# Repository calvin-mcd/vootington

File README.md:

# Vootington

The Vootington is an open source hall-effect pcb for the V4N keyboard.

The aim of this project is to offer a functional hardware Hall-effect reference project for the community. The project is not meant to offer the full aspects of firmware. I leave that to smart people to figure out.

The keyboard takes design cues from the Wooting keyboards, [the moonpad](https://github.com/RephlexZero/MoonPad) and [the void switch keyboards](https://github.com/riskable/void_switch_65_pct) from riskable.

## Layout

[Link](http://www.keyboard-layout-editor.com/#/gists/a01bb022278fa95758b773367ecef891)

## Firmware

The basic firmware included in the folder is experimental and designed by KarlK90. Their work can be found here:
https://github.com/KarlK90/qmk_firmware/tree/feature/vootington/keyboards/calvin0563/vootington

Pete is currently developing more advanced HE firmware for zmk. Keep your eyes on that:
https://github.com/petejohanson/vootington-zmk-config

**beware!!!**

The hardware configuration for rgb on the vootington is currently not supported by zmk, which means no rgb with the zmk firmware.

## Todo

- [ ] create advanced firmware with full HE functionality

## Disclaimer

This PCB has been fully tested and is confirmed to work. However, no-one involved in this project is responsible for any usage issues that may arise. Order at your own risk. Feel free to edit, modify and otherwise utilise these files.

## License

This project is released under the GPL v3 License. Please refer to the LICENCE file.

## Credits

big thanks to KarlK90 for making the initial firmware and for supporting the hardware design of the keyboard.

another huge thanks to pete for writing zmk firmware for this!

As always big thanks also to the many people who helped to inspire this board!

Any questions, contact Calvin0563 on Discord.

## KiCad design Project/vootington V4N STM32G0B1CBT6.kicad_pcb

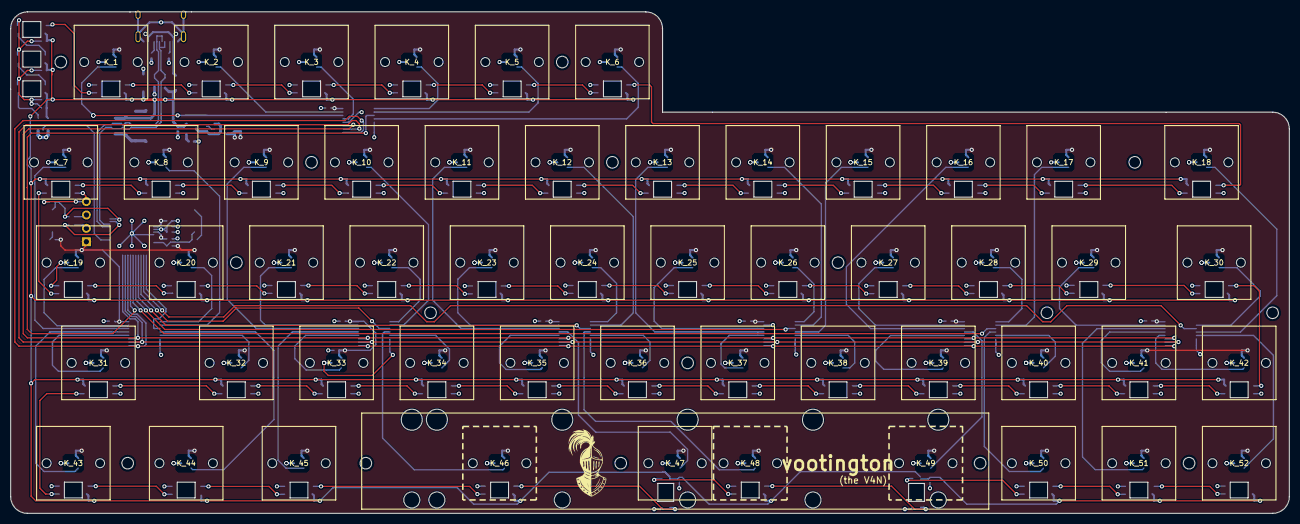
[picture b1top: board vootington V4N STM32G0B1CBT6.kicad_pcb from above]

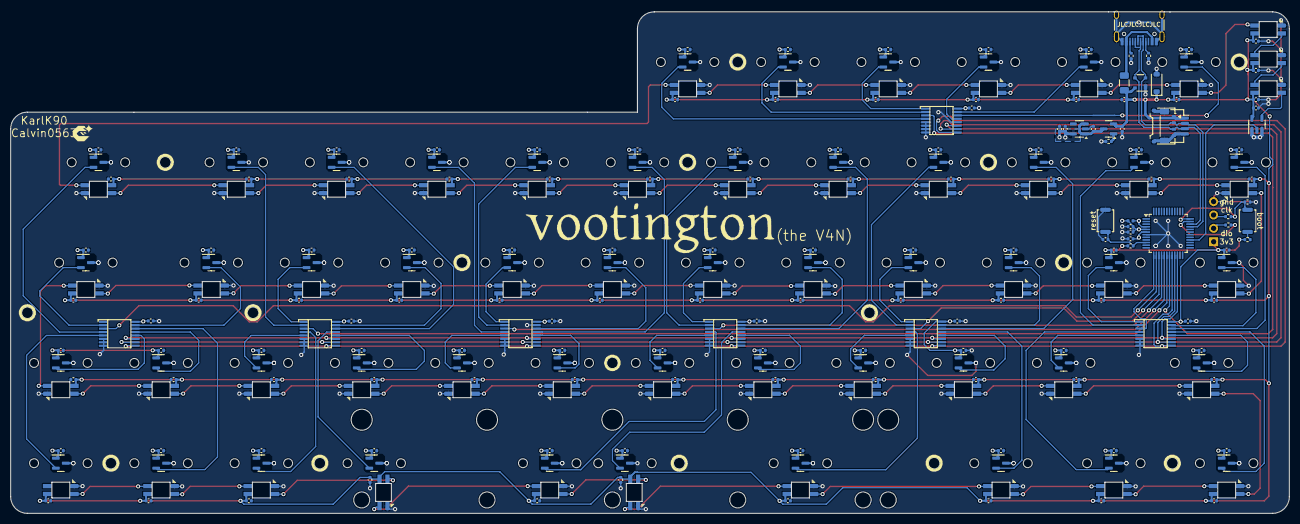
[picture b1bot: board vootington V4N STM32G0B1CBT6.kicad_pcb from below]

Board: 2 copper layers, 242.9 x 95.2 mm, 331 parts (260 on the bottom side), 135 nets.

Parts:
C1, C2, C3, C4, C5, C6, C7, C8, C9, C10, C11, C12, C13, C14, C15, C16, C17, C18, C19, C20, C21, C22, C23, C24, C25, C26, C27, C28, C29, C30, C31, C32, C33, C34, C35, C36, C37, C38, C39, C40, C41, C42, C43, C44, C45, C46, C47, C48, C49, C50, C51, C52, C53, C56, C60, C61, C62, C63, C64, C65, C66, C67, C68, C69, C70, C71, C72, C73, C74, C75, C76, C77, C78, C79, C80, C81, C82, C83, C84, C85, C86, C87, C88, C89, C90, C91, C92, C93, C94, C95, C96, C97, C98, C99, C100, C101, C102, C103, C104, C105, C106, C107, C108, C109, C110, C111, C112, C113, C114, C115, C116, C117: 100nF; C_0402_1005Metric
C54: 10nF; C_0402_1005Metric
C55: 1uF; C_0402_1005Metric
C57, C58: 10uF; C_0402_1005Metric
C59: 2.2uF; C_0402_1005Metric
C118, C119, C120, C121, C122, C123, C124: 100pF; C_0402_1005Metric
D1, D2, D3, D4, D5, D6, D7, D8, D9, D10, D11, D12, D13, D14, D15, D16, D17, D18, D19, D20, D21, D22, D23, D24, D25, D26, D27, D28, D29, D30, D31, D32, D33, D34, D35, D36, D37, D38, D39, D40, D41, D42, D43, D44, D45, D46, D47, D48, D49, D50, D51, D52, D53, D54, D55: YS-SK6803MINI-E; SK6803-MINI-E
D_PWR1: SMF9.0CA; D_SOD-123
F1: 500mA; Fuse_1206_3216Metric
FB1: 1k OHM 100mhz; Fuse_0402_1005Metric
H1, H2, H3, H4, H5, H6, H7, H8, H9, H10, H11, H12, H13, H14, H15, H16: MountingHole; HOLE_M2
J1: Conn_01x04; PinHeader_1x04_P2.54mm_Vertical
J2: USB_C sink board 1.3mm; USB_C_Receptacle_HRO_TYPE-C-31-M-12
J3: JST SH; JST_SH_SM04B-SRSS-TB_1x04-1MP_P1.00mm_Horizontal
J4: Pico EZmate; Molex_Pico-EZmate_78171-0004_1x04-1MP_P1.20mm_Vertical
K_1, K_2, K_3, K_4, K_5, K_6, K_7, K_8, K_9, K_10, K_11, K_12, K_13, K_14, K_15, K_16, K_17, K_18, K_19, K_20, K_21, K_22, K_23, K_24, K_25, K_26, K_27, K_28, K_29, K_30, K_31, K_32, K_33, K_34, K_35, K_36, K_37, K_38, K_39, K_40, K_41, K_42, K_43, K_44, K_45, K_46, K_47, K_48, K_49, K_50, K_51, K_52: KEYSW; Wooting_1.00u
Q1: AP40P05; SOT-23
R1, R2: 33 Ohm; R_0402_1005Metric
R3, R5, R6: 10k; R_0402_1005Metric
R4: 330 Ohm; R_0402_1005Metric
R7, R8: 5.1k; R_0402_1005Metric
S1: MX_stab; STAB_MX_2.75u
S2: MX_stab; STAB_MX_6.25u
S3: MX_stab; STAB_MX_2.25u
SW1, SW2: Alps SKRK; SW_Push_SPST_NO_Alps_SKRK
U1, U2, U3, U4, U5, U6, U7, U8, U9, U10, U11, U12, U13, U14, U15, U16, U17, U18, U19, U20, U21, U22, U23, U24, U25, U26, U27, U28, U29, U30, U31, U32, U33, U34, U35, U36, U37, U38, U39, U40, U41, U42, U43, U44, U45, U46, U47, U48, U49, U50, U51, U52: SLSS49E-3; SOT-23
U53: STM32G0B1CBTx; LQFP-48_7x7mm_P0.5mm
U54: AP2112K-3.3; SOT-23-5
U55: PRTR5V0U2X; SOT-143
U56: 74AHCT1G125; TSOT-23-5
U57, U58, U59, U60, U61, U62, U63: 74HC4051; TSSOP16

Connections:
+3V3: C1.1, C2.1, C3.1, C4.1, C5.1, C6.1, C7.1, C8.1, C9.1, C10.1, C11.1, C12.1, C13.1, C14.1, C15.1, C16.1, C17.1, C18.1, C19.1, C20.1, C21.1, C22.1, C23.1, C24.1, C25.1, C26.1, C27.1, C28.1, C29.1, C30.1, C31.1, C32.1, C33.1, C34.1, C35.1, C36.1, C37.1, C38.1, C39.1, C40.1, C41.1, C42.1, C43.1, C44.1, C45.1, C46.1, C47.1, C48.1, C49.1, C50.1, C51.1, C52.1, C53.1, C58.2, C59.2, C118.1, C119.1, C120.1, C121.1, C122.1, C123.1, C124.1, FB1.1, J1.1, R3.1, R4.1, U1.1 (VDD), U2.1 (VDD), U3.1 (VDD), U4.1 (VDD), U5.1 (VDD), U6.1 (VDD), U7.1 (VDD), U8.1 (VDD), U9.1 (VDD), U10.1 (VDD), U11.1 (VDD), U12.1 (VDD), U13.1 (VDD), U14.1 (VDD), U15.1 (VDD), U16.1 (VDD), U17.1 (VDD), U18.1 (VDD), U19.1 (VDD), U20.1 (VDD), U21.1 (VDD), U22.1 (VDD), U23.1 (VDD), U24.1 (VDD), U25.1 (VDD), U26.1 (VDD), U27.1 (VDD), U28.1 (VDD), U29.1 (VDD), U30.1 (VDD), U31.1 (VDD), U32.1 (VDD), U33.1 (VDD), U34.1 (VDD), U35.1 (VDD), U36.1 (VDD), U37.1 (VDD), U38.1 (VDD), U39.1 (VDD), U40.1 (VDD), U41.1 (VDD), U42.1 (VDD), U43.1 (VDD), U44.1 (VDD), U45.1 (VDD), U46.1 (VDD), U47.1 (VDD), U48.1 (VDD), U49.1 (VDD), U50.1 (VDD), U51.1 (VDD), U52.1 (VDD), U53.4 (VBAT), U53.6 (VDD), U54.5 (VOUT), U57.16 (VCC), U58.16 (VCC), U59.16 (VCC), U60.16 (VCC), U61.16 (VCC), U62.16 (VCC), U63.16 (VCC)
+5V: C60.2, C61.1, C62.1, C63.1, C64.1, C65.2, C66.1, C67.1, C68.1, C69.1, C70.1, C71.1, C72.1, C73.1, C74.1, C75.1, C76.1, C77.1, C78.1, C79.1, C80.1, C81.1, C82.1, C83.1, C84.1, C85.1, C86.1, C87.1, C88.1, C89.1, C90.1, C91.1, C92.1, C93.1, C94.1, C95.1, C96.1, C97.1, C98.1, C99.1, C100.1, C101.1, C102.1, C103.1, C104.1, C105.1, C106.1, C107.1, C108.1, C109.1, C110.1, C111.1, C112.1, C113.1, C114.1, C115.1, C116.1, C117.1, D1.3 (VDD), D2.3 (VDD), D3.3 (VDD), D4.3 (VDD), D5.3 (VDD), D6.3 (VDD), D7.3 (VDD), D8.3 (VDD), D9.3 (VDD), D10.3 (VDD), D11.3 (VDD), D12.3 (VDD), D13.3 (VDD), D14.3 (VDD), D15.3 (VDD), D16.3 (VDD), D17.3 (VDD), D18.3 (VDD), D19.3 (VDD), D20.3 (VDD), D21.3 (VDD), D22.3 (VDD), D23.3 (VDD), D24.3 (VDD), D25.3 (VDD), D26.3 (VDD), D27.3 (VDD), D28.3 (VDD), D29.3 (VDD), D30.3 (VDD), D31.3 (VDD), D32.3 (VDD), D33.3 (VDD), D34.3 (VDD), D35.3 (VDD), D36.3 (VDD), D37.3 (VDD), D38.3 (VDD), D39.3 (VDD), D40.3 (VDD), D41.3 (VDD), D42.3 (VDD), D43.3 (VDD), D44.3 (VDD), D45.3 (VDD), D46.3 (VDD), D47.3 (VDD), D48.3 (VDD), D49.3 (VDD), D50.3 (VDD), D51.3 (VDD), D52.3 (VDD), D53.3 (VDD), D54.3 (VDD), D55.3 (VDD), D_PWR1.1 (A1), F1.2, J3.1, J4.1, Q1.2 (S), U55.4 (VCC), U56.5 (VCC)
/MCU/VREF: C54.1, C55.1, FB1.2, U53.5 (VREF+)
ADC0: U53.14 (PA3), U57.3 (A)
ADC1: U53.18 (PA7), U58.3 (A)
ADC2: U53.17 (PA6), U59.3 (A)
ADC3: U53.16 (PA5), U60.3 (A)
ADC4: U53.15 (PA4), U61.3 (A)
ADC5: U53.13 (PA2), U62.3 (A)
ADC6: U53.19 (PB0), U63.3 (A)
BOOT0: R2.1, R5.1, SW1.2, U53.36 (PA14)
D_N: J2.A7 (D-), J2.B7 (D-), J3.2, J4.2, U53.33 (PA11/PA9), U55.2 (I/O1)
D_P: J2.A6 (D+), J2.B6 (D+), J3.3, J4.3, U53.34 (PA12/PA10), U55.3 (I/O2)
GND: C1.2, C2.2, C3.2, C4.2, C5.2, C6.2, C7.2, C8.2, C9.2, C10.2, C11.2, C12.2, C13.2, C14.2, C15.2, C16.2, C17.2, C18.2, C19.2, C20.2, C21.2, C22.2, C23.2, C24.2, C25.2, C26.2, C27.2, C28.2, C29.2, C30.2, C31.2, C32.2, C33.2, C34.2, C35.2, C36.2, C37.2, C38.2, C39.2, C40.2, C41.2, C42.2, C43.2, C44.2, C45.2, C46.2, C47.2, C48.2, C49.2, C50.2, C51.2, C52.2, C53.2, C54.2, C55.2, C56.2, C57.1, C58.1, C59.1, C60.1, C61.2, C62.2, C63.2, C64.2, C65.1, C66.2, C67.2, C68.2, C69.2, C70.2, C71.2, C72.2, C73.2, C74.2, C75.2, C76.2, C77.2, C78.2, C79.2, C80.2, C81.2, C82.2, C83.2, C84.2, C85.2, C86.2, C87.2, C88.2, C89.2, C90.2, C91.2, C92.2, C93.2, C94.2, C95.2, C96.2, C97.2, C98.2, C99.2, C100.2, C101.2, C102.2, C103.2, C104.2, C105.2, C106.2, C107.2, C108.2, C109.2, C110.2, C111.2, C112.2, C113.2, C114.2, C115.2, C116.2, C117.2, C118.2, C119.2, C120.2, C121.2, C122.2, C123.2, C124.2, D1.1 (VSS), D2.1 (VSS), D3.1 (VSS), D4.1 (VSS), D5.1 (VSS), D6.1 (VSS), D7.1 (VSS), D8.1 (VSS), D9.1 (VSS), D10.1 (VSS), D11.1 (VSS), D12.1 (VSS), D13.1 (VSS), D14.1 (VSS), D15.1 (VSS), D16.1 (VSS), D17.1 (VSS), D18.1 (VSS), D19.1 (VSS), D20.1 (VSS), D21.1 (VSS), D22.1 (VSS), D23.1 (VSS), D24.1 (VSS), D25.1 (VSS), D26.1 (VSS), D27.1 (VSS), D28.1 (VSS), D29.1 (VSS), D30.1 (VSS), D31.1 (VSS), D32.1 (VSS), D33.1 (VSS), D34.1 (VSS), D35.1 (VSS), D36.1 (VSS), D37.1 (VSS), D38.1 (VSS), D39.1 (VSS), D40.1 (VSS), D41.1 (VSS), D42.1 (VSS), D43.1 (VSS), D44.1 (VSS), D45.1 (VSS), D46.1 (VSS), D47.1 (VSS), D48.1 (VSS), D49.1 (VSS), D50.1 (VSS), D51.1 (VSS), D52.1 (VSS), D53.1 (VSS), D54.1 (VSS), D55.1 (VSS), D_PWR1.2 (A2), J1.4, J2.A1 (GND), J2.A12 (GND), J2.B1 (GND), J2.B12 (GND), J2.S1 (SHIELD), J3.4, J3.MP (MountPin), J4.4, J4.MP (MountPin), R5.2, R6.1, R7.1, R8.1, SW2.2, U1.3 (GND), U2.3 (GND), U3.3 (GND), U4.3 (GND), U5.3 (GND), U6.3 (GND), U7.3 (GND), U8.3 (GND), U9.3 (GND), U10.3 (GND), U11.3 (GND), U12.3 (GND), U13.3 (GND), U14.3 (GND), U15.3 (GND), U16.3 (GND), U17.3 (GND), U18.3 (GND), U19.3 (GND), U20.3 (GND), U21.3 (GND), U22.3 (GND), U23.3 (GND), U24.3 (GND), U25.3 (GND), U26.3 (GND), U27.3 (GND), U28.3 (GND), U29.3 (GND), U30.3 (GND), U31.3 (GND), U32.3 (GND), U33.3 (GND), U34.3 (GND), U35.3 (GND), U36.3 (GND), U37.3 (GND), U38.3 (GND), U39.3 (GND), U40.3 (GND), U41.3 (GND), U42.3 (GND), U43.3 (GND), U44.3 (GND), U45.3 (GND), U46.3 (GND), U47.3 (GND), U48.3 (GND), U49.3 (GND), U50.3 (GND), U51.3 (GND), U52.3 (GND), U53.7 (VSS), U54.2 (GND), U55.1 (GND), U56.1, U56.3 (GND), U57.6 (~E), U57.7 (VEE), U57.8 (GND), U58.6 (~E), U58.7 (VEE), U58.8 (GND), U59.6 (~E), U59.7 (VEE), U59.8 (GND), U59.15 (A2), U60.6 (~E), U60.7 (VEE), U60.8 (GND), U61.6 (~E), U61.7 (VEE), U61.8 (GND), U62.6 (~E), U62.7 (VEE), U62.8 (GND), U63.5 (A5), U63.6 (~E), U63.7 (VEE), U63.8 (GND), U63.12 (A3)
K_1: U7.2 (OUT), U62.14 (A1)
K_2: U8.2 (OUT), U62.2 (A6)
K_3: U9.2 (OUT), U61.14 (A1)
K_4: U10.2 (OUT), U61.2 (A6)
K_5: U11.2 (OUT), U60.14 (A1)
K_6: U12.2 (OUT), U60.2 (A6)
K_7: U13.2 (OUT), U59.13 (A0)
K_8: U14.2 (OUT), U59.2 (A6)
K_9: U15.2 (OUT), U59.4 (A7)
K_10: U16.2 (OUT), U58.14 (A1)
K_11: U18.2 (OUT), U58.2 (A6)
K_12: U17.2 (OUT), U57.4 (A7)
K_13: U19.2 (OUT), U62.15 (A2)
K_14: U20.2 (OUT), U62.1 (A4)
K_15: U21.2 (OUT), U61.15 (A2)
K_16: U22.2 (OUT), U61.1 (A4)
K_17: U23.2 (OUT), U60.15 (A2)
K_18: U24.2 (OUT), U60.1 (A4)
K_19: U25.2 (OUT), U59.14 (A1)
K_20: U26.2 (OUT), U59.1 (A4)
K_21: U27.2 (OUT), U58.15 (A2)
K_22: U28.2 (OUT), U58.1 (A4)
K_23: U29.2 (OUT), U57.15 (A2)
K_24: U30.2 (OUT), U57.2 (A6)
K_25: U31.2 (OUT), U62.12 (A3)
K_26: U32.2 (OUT), U62.5 (A5)
K_27: U33.2 (OUT), U61.12 (A3)
K_28: U34.2 (OUT), U61.5 (A5)
K_29: U35.2 (OUT), U60.12 (A3)
K_30: U36.2 (OUT), U60.5 (A5)
K_31: U37.2 (OUT), U59.12 (A3)
K_32: U38.2 (OUT), U59.5 (A5)
K_33: U39.2 (OUT), U58.12 (A3)
K_34: U40.2 (OUT), U58.5 (A5)
K_35: U41.2 (OUT), U57.13 (A0)
K_36: U42.2 (OUT), U57.12 (A3)
K_37: U43.2 (OUT), U62.13 (A0)
K_38: U44.2 (OUT), U62.4 (A7)
K_39: U45.2 (OUT), U61.13 (A0)
K_40: U46.2 (OUT), U61.4 (A7)
K_41: U47.2 (OUT), U60.13 (A0)
K_42: U48.2 (OUT), U60.4 (A7)
K_43: U49.2 (OUT), U58.13 (A0)
K_44: U50.2 (OUT), U58.4 (A7)
K_45: U51.2 (OUT), U57.14 (A1)
K_46: U52.2 (OUT), U57.5 (A5)
K_48: U1.2 (OUT), U63.14 (A1)
K_49: U2.2 (OUT), U63.15 (A2)
K_50: U3.2 (OUT), U63.13 (A0)
K_51: U4.2 (OUT), U63.1 (A4)
K_52: U5.2 (OUT), U63.2 (A6)
K_53: U6.2 (OUT), U63.4 (A7)
NRST: C56.1, R3.2, SW2.1, U53.10 (PF2)
unnamed: D1.4 (DOUT), D2.2 (DIN)
unnamed: D2.4 (DOUT), D3.2 (DIN)
unnamed: D3.4 (DOUT), D4.2 (DIN)
unnamed: D4.4 (DOUT), D5.2 (DIN)
unnamed: D5.4 (DOUT), D6.2 (DIN)
unnamed: D6.4 (DOUT), D7.2 (DIN)
unnamed: D7.4 (DOUT), D8.2 (DIN)
unnamed: D8.4 (DOUT), D9.2 (DIN)
unnamed: D9.4 (DOUT), D10.2 (DIN)
unnamed: D10.4 (DOUT), D11.2 (DIN)
unnamed: D11.4 (DOUT), D12.2 (DIN)
unnamed: D12.4 (DOUT), D13.2 (DIN)
unnamed: D13.4 (DOUT), D14.2 (DIN)
unnamed: D14.4 (DOUT), D15.2 (DIN)
unnamed: D15.4 (DOUT), D16.2 (DIN)
unnamed: D16.4 (DOUT), D17.2 (DIN)
unnamed: D17.4 (DOUT), D18.2 (DIN)
unnamed: D18.4 (DOUT), D19.2 (DIN)
unnamed: D19.4 (DOUT), D20.2 (DIN)
unnamed: D20.4 (DOUT), D21.2 (DIN)
unnamed: D21.4 (DOUT), D33.2 (DIN)
unnamed: D22.2 (DIN), D23.4 (DOUT)
unnamed: D22.4 (DOUT), D34.2 (DIN)
unnamed: D23.2 (DIN), D24.4 (DOUT)
unnamed: D24.2 (DIN), D25.4 (DOUT)
unnamed: D25.2 (DIN), D26.4 (DOUT)
unnamed: D26.2 (DIN), D27.4 (DOUT)
unnamed: D27.2 (DIN), D28.4 (DOUT)
unnamed: D28.2 (DIN), D29.4 (DOUT)
unnamed: D29.2 (DIN), D30.4 (DOUT)
unnamed: D30.2 (DIN), D31.4 (DOUT)
unnamed: D31.2 (DIN), D32.4 (DOUT)
unnamed: D32.2 (DIN), D33.4 (DOUT)
unnamed: D34.4 (DOUT), D35.2 (DIN)
unnamed: D35.4 (DOUT), D36.2 (DIN)
unnamed: D36.4 (DOUT), D37.2 (DIN)
unnamed: D37.4 (DOUT), D38.2 (DIN)
unnamed: D38.4 (DOUT), D39.2 (DIN)
unnamed: D39.4 (DOUT), D40.2 (DIN)
unnamed: D40.4 (DOUT), D41.2 (DIN)
unnamed: D41.4 (DOUT), D42.2 (DIN)
unnamed: D42.4 (DOUT), D43.2 (DIN)
unnamed: D43.4 (DOUT), D44.2 (DIN)
unnamed: D44.4 (DOUT), D45.2 (DIN)
unnamed: D45.4 (DOUT), D55.2 (DIN)
unnamed: D46.2 (DIN), D47.4 (DOUT)
unnamed: D47.2 (DIN), D48.4 (DOUT)
unnamed: D48.2 (DIN), D49.4 (DOUT)
unnamed: D49.2 (DIN), D50.4 (DOUT)
unnamed: D50.2 (DIN), D51.4 (DOUT)
unnamed: D51.2 (DIN), D52.4 (DOUT)
unnamed: D52.2 (DIN), D53.4 (DOUT)
unnamed: D53.2 (DIN), D54.4 (DOUT)
unnamed: D54.2 (DIN), D55.4 (DOUT)
unnamed: J1.2, R1.2
unnamed: J1.3, R2.2
unnamed: J2.A5 (CC1), R7.2
unnamed: J2.B5 (CC2), R8.2
unnamed: C57.2, Q1.3 (D), U54.1 (VIN), U54.3 (EN)
unnamed: Q1.1 (G), R6.2
unnamed: R4.2, SW1.1
RGB: D1.2 (DIN), U56.4
RGB MCU: U53.28 (PA8), U56.2
SELECT0: U53.22 (PB10), U57.11 (S0), U58.11 (S0), U59.11 (S0), U60.11 (S0), U61.11 (S0), U62.11 (S0), U63.11 (S0)
SELECT1: U53.21 (PB2), U57.10 (S1), U58.10 (S1), U59.10 (S1), U60.10 (S1), U61.10 (S1), U62.10 (S1), U63.10 (S1)
SELECT2: U53.20 (PB1), U57.9 (S2), U58.9 (S2), U59.9 (S2), U60.9 (S2), U61.9 (S2), U62.9 (S2), U63.9 (S2)
SWDIO: R1.1, U53.35 (PA13)
VBUS: F1.1, J2.A4 (VBUS), J2.A9 (VBUS), J2.B4 (VBUS), J2.B9 (VBUS)

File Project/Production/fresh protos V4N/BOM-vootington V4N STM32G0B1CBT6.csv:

Comment,Designator,Footprint,LCSC,Quantity,
330 Ohm,R4,R_0402_1005Metric,C105875,1,
1uF,C55,C_0402_1005Metric,C106254,1,
Alps SKRK,"SW1,SW2",SW_Push_SPST_NO_Alps_SKRK,C115351,2,
1k OHM 100mhz,FB1,Fuse_0402_1005Metric,C76883,1,
33 Ohm,"R1,R2",R_0402_1005Metric,C137880,2,
10nF,C54,C_0402_1005Metric,C1524,1,
JST SH,J3,JST_SH_SM04B-SRSS-TB_1x04-1MP_P1.00mm_Horizontal,C160404,1,
10k,"R3,R5,R6",R_0402_1005Metric,C25744,3,
5.1k,"R7,R8",R_0402_1005Metric,C25905,2,
PRTR5V0U2X,U55,SOT-143,C2827688,1,
STM32G0B1CBTx,U53,LQFP-48_7x7mm_P0.5mm,C2847904,1,
AP40P05,Q1,SOT-23,C2886385,1,
SLSS49E-3,"U1,U10,U11,U12,U13,U14,U15,U16,U17,U18,U19,U2,U20,U21,U22,U23,U24,U25,U26,U27,U28,U29,U3,U30,U31,U32,U33,U34,U35,U36,U37,U38,U39,U4,U40,U41,U42,U43,U44,U45,U46,U47,U48,U49,U5,U50,U51,U52,U6,U7,U8,U9",SOT-23,C2904393,52,
SMF9.0CA,D_PWR1,D_SOD-123,C2980405,1,
USB_C sink board 1.3mm,J2,USB_C_Receptacle_HRO_TYPE-C-31-M-12,C165948,1,
AP2112K-3.3,U54,SOT-23-5,C3021085,1,
100nF,"C1,C10,C100,C101,C102,C103,C104,C105,C106,C107,C108,C109,C11,C110,C111,C112,C113,C114,C115,C116,C117,C118,C119,C12,C120,C121,C122,C123,C124,C13,C14,C15,C16,C17,C18,C19,C2,C20,C21,C22,C23,C24,C25,C26,C27,C28,C29,C3,C30,C31,C32,C33,C34,C35,C36,C37,C38,C39,C4,C40,C41,C42,C43,C44,C45,C46,C47,C48,C49,C5,C50,C51,C52,C53,C56,C6,C61,C62,C63,C64,C65,C66,C67,C68,C69,C7,C70,C71,C72,C73,C74,C75,C76,C77,C78,C79,C8,C80,C81,C82,C83,C84,C85,C86,C87,C88,C89,C9,C90,C91,C92,C93,C94,C95,C96,C97,C98,C99",C_0402_1005Metric,C307331,118,
YS-SK6803MINI-E,"D1,D10,D11,D12,D13,D14,D15,D16,D17,D18,D19,D2,D20,D21,D22,D23,D24,D25,D26,D27,D28,D29,D3,D30,D31,D32,D33,D34,D35,D36,D37,D38,D39,D4,D40,D41,D42,D43,D44,D45,D46,D47,D48,D49,D5,D50,D51,D52,D53,D54,D55,D6,D7,D8,D9",SK6803-MINI-E,C5242955,55,C5242955
10uF,"C57,C58,C59,C60",C_0402_1005Metric,C52923,4,
74HC4051,"U57,U58,U59,U60,U61,U62,U63",TSSOP16,C5645,7,
500mA,F1,Fuse_1206_3216Metric,C369160,1,
74AHCT1G125,U56,TSOT-23-5,C7468,1,

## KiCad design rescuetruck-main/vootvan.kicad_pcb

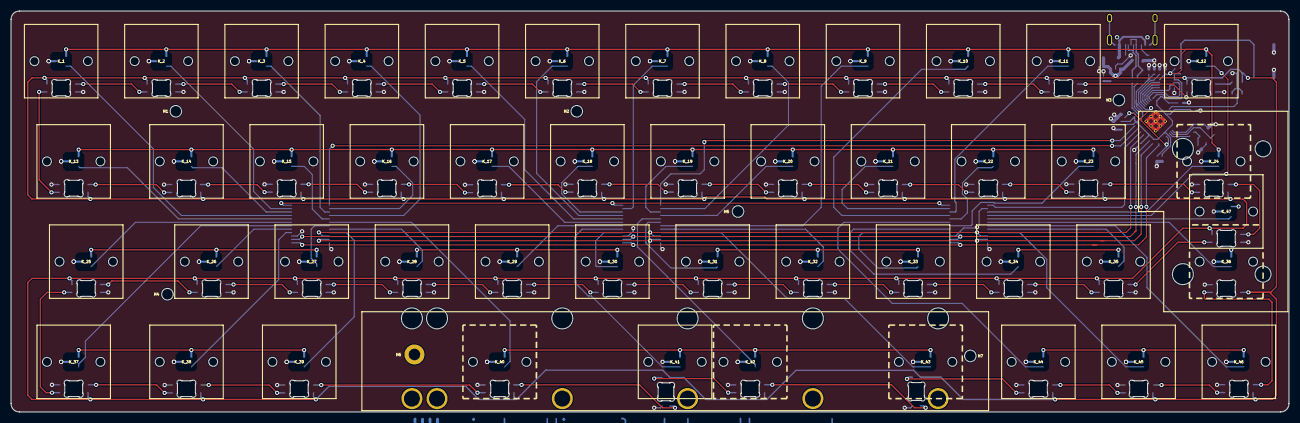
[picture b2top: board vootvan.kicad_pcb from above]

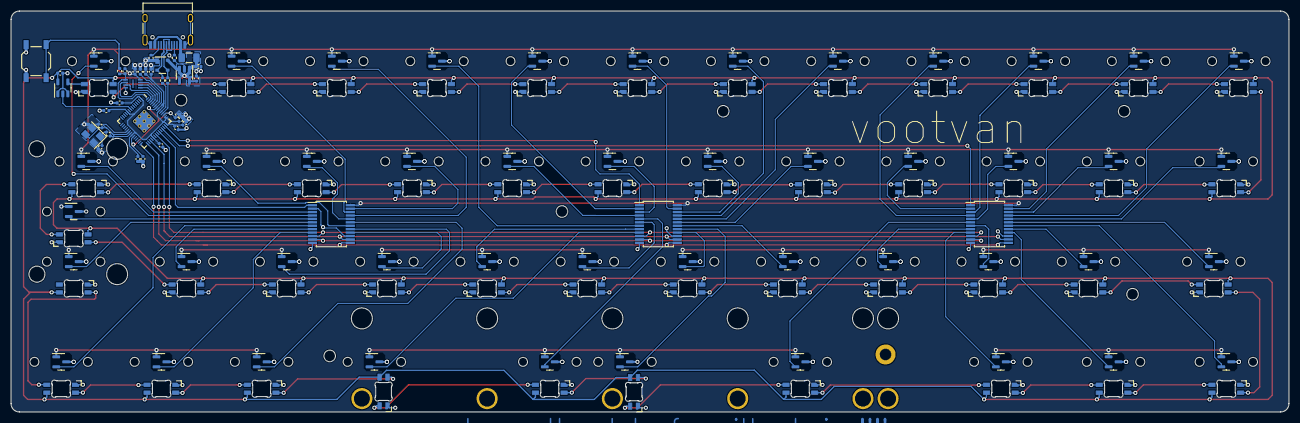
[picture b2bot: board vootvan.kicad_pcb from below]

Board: 2 copper layers, 242.9 x 76.2 mm, 189 parts (131 on the bottom side), 123 nets.

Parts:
AM1, AM2, AM3: CD74HC4067SM; SSOP-24_5.3x8.2mm_P0.65mm
C1, C2, C20, C21: 1u; C_0402_1005Metric
C3: 100nF; C_0402_1005Metric
C10, C11, C12, C13, C14, C15, C16, C17, C18, C19, C22: 100n; C_0402_1005Metric
C23, C24: 27p; C_0402_1005Metric
D1: PRTR5V0U2X; SOT-143
D2, D7, D8, D13, D14, D19, D20, D25, D26, D31, D32, D37, D38, D44, D49: SK6812MINI-E; LED_6028R
D3, D4, D5, D6, D9, D10, D11, D12, D15, D16, D17, D18, D21, D22, D23, D24, D27, D28, D29, D30, D33, D34, D35, D36, D39, D40, D41, D42, D45, D46, D47, D48: SK6812MINI; LED_6028R
F1: 1.1A; Fuse_1206_3216Metric
H1, H2, H3, H4, H5, H7: MountingHole; MountingHole_2.2mm_M2
H6: MountingHole; MountingHole_2.2mm_M2_DIN965_Pad
IC1: W25Q16JVUXIQ; SON50P300X200X60-9N
J1: USB-C 2.0 Receptacle; USB_C_Receptacle_HRO_TYPE-C-31-M-12
K_1, K_2, K_3, K_4, K_5, K_6, K_7, K_8, K_9, K_10, K_11, K_12, K_13, K_14, K_15, K_16, K_17, K_18, K_19, K_20, K_21, K_22, K_23, K_24, K_25, K_26, K_27, K_28, K_29, K_30, K_31, K_32, K_33, K_34, K_35, K_36, K_37, K_38, K_39, K_40, K_41, K_42, K_43, K_44, K_45, K_46, K_47: KEYSW; Wooting_1.00u
R1, R2: 5.1k; R_0402_1005Metric
R7, R8: 27; R_0402_1005Metric
R9: DNP; C_0402_1005Metric
R10, R11: 1k; R_0402_1005Metric
S1: MX_stab; STAB_MX_P_2.75u
S2: MX_stab; STAB_MX_P_6.25u
S3: MX_stab; STAB_MX_P_2.25u
S4: MX_stab; STAB_MX_ISO-ROT
SW2: Reset; SW_SPST_TL3342
U1: AP2112K-3.3; SOT-23-5
U2, U4, U5, U6, U7, U8, U9, U10, U11, U12, U13, U14, U15, U16, U17, U18, U19, U20, U21, U22, U23, U24, U25, U26, U27, U28, U29, U30, U31, U32, U33, U34, U35, U36, U37, U38, U39, U40, U41, U42, U43, U44, U45, U47, U48, U49, U50: SLSS49E-3; SOT-23
U3: RP2040; RP2040-QFN-56
U46: 74AHCT1G125; TSOT-23-5
Y2: JGHC S3212000181080; Crystal_SMD_3225-4Pin_3.2x2.5mm

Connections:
+1V1: C10.1, C11.1, C20.1, U3.23 (DVDD), U3.45 (VREG_VOUT), U3.50 (DVDD)
+3V3: AM1.24 (VCC), AM2.24 (VCC), AM3.24 (VCC), C2.1, C12.1, C13.1, C14.1, C15.1, C16.1, C17.1, C18.1, C19.1, C21.1, C22.1, IC1.8 (VCC), R9.1, U1.5 (VOUT), U2.1 (VDD), U3.1 (IOVDD), U3.10 (IOVDD), U3.22 (IOVDD), U3.33 (IOVDD), U3.42 (IOVDD), U3.43 (ADC_AVDD), U3.44 (VREG_IN), U3.48 (USB_VDD), U3.49 (IOVDD), U4.1 (VDD), U5.1 (VDD), U6.1 (VDD), U7.1 (VDD), U8.1 (VDD), U9.1 (VDD), U10.1 (VDD), U11.1 (VDD), U12.1 (VDD), U13.1 (VDD), U14.1 (VDD), U15.1 (VDD), U16.1 (VDD), U17.1 (VDD), U18.1 (VDD), U19.1 (VDD), U20.1 (VDD), U21.1 (VDD), U22.1 (VDD), U23.1 (VDD), U24.1 (VDD), U25.1 (VDD), U26.1 (VDD), U27.1 (VDD), U28.1 (VDD), U29.1 (VDD), U30.1 (VDD), U31.1 (VDD), U32.1 (VDD), U33.1 (VDD), U34.1 (VDD), U35.1 (VDD), U36.1 (VDD), U37.1 (VDD), U38.1 (VDD), U39.1 (VDD), U40.1 (VDD), U41.1 (VDD), U42.1 (VDD), U43.1 (VDD), U44.1 (VDD), U45.1 (VDD), U47.1 (VDD), U48.1 (VDD), U49.1 (VDD), U50.1 (VDD)
+5V: C1.1, C3.2, D1.4 (VCC), D2.1 (VDD), D3.1 (VDD), D4.1 (VDD), D5.1 (VDD), D6.1 (VDD), D7.1 (VDD), D8.1 (VDD), D9.1 (VDD), D10.1 (VDD), D11.1 (VDD), D12.1 (VDD), D13.1 (VDD), D14.1 (VDD), D15.1 (VDD), D16.1 (VDD), D17.1 (VDD), D18.1 (VDD), D19.1 (VDD), D20.1 (VDD), D21.1 (VDD), D22.1 (VDD), D23.1 (VDD), D24.1 (VDD), D25.1 (VDD), D26.1 (VDD), D27.1 (VDD), D28.1 (VDD), D29.1 (VDD), D30.1 (VDD), D31.1 (VDD), D32.1 (VDD), D33.1 (VDD), D34.1 (VDD), D35.1 (VDD), D36.1 (VDD), D37.1 (VDD), D38.1 (VDD), D39.1 (VDD), D40.1 (VDD), D41.1 (VDD), D42.1 (VDD), D44.1 (VDD), D45.1 (VDD), D46.1 (VDD), D47.1 (VDD), D48.1 (VDD), D49.1 (VDD), F1.2, U1.1 (VIN), U1.3 (EN), U46.5 (VCC)
/MCU/QSPI_SCLK: IC1.6 (CLK), U3.52 (QSPI_SCLK)
/MCU/QSPI_SD0: IC1.5 (DI_IO0), U3.53 (QSPI_SD0)
/MCU/QSPI_SD1: IC1.2 (DO_IO1), U3.55 (QSPI_SD1)
/MCU/QSPI_SD2: IC1.3 (~WP_IO2), U3.54 (QSPI_SD2)
/MCU/QSPI_SD3: IC1.7 (~RESET_IO3), U3.51 (QSPI_SD3)
/MCU/QSPI_SS: IC1.1 (~CS), R9.2, R10.1, U3.56 (QSPI_SS)
/MCU/XIN: C23.1, U3.20 (XIN), Y2.3
/MCU/XOUT: R11.1, U3.21 (XOUT)
/MCU/~USB_BOOT: R10.2, SW2.2
AM0: AM1.1 (COM), U3.39 (GPIO27_ADC1)
AM1: AM2.1 (COM), U3.41 (GPIO29_ADC3)
AM2: AM3.1 (COM), U3.37 (GPIO25)
GND: AM1.12 (GND), AM1.15 (~E), AM2.12 (GND), AM2.15 (~E), AM3.2 (I7), AM3.12 (GND), AM3.15 (~E), C1.2, C2.2, C3.1, C10.2, C11.2, C12.2, C13.2, C14.2, C15.2, C16.2, C17.2, C18.2, C19.2, C20.2, C21.2, C22.2, C23.2, C24.2, D1.1 (GND), D2.4 (VSS), D3.4 (VSS), D4.4 (VSS), D5.4 (VSS), D6.4 (VSS), D7.4 (VSS), D8.4 (VSS), D9.4 (VSS), D10.4 (VSS), D11.4 (VSS), D12.4 (VSS), D13.4 (VSS), D14.4 (VSS), D15.4 (VSS), D16.4 (VSS), D17.4 (VSS), D18.4 (VSS), D19.4 (VSS), D20.4 (VSS), D21.4 (VSS), D22.4 (VSS), D23.4 (VSS), D24.4 (VSS), D25.4 (VSS), D26.4 (VSS), D27.4 (VSS), D28.4 (VSS), D29.4 (VSS), D30.4 (VSS), D31.4 (VSS), D32.4 (VSS), D33.4 (VSS), D34.4 (VSS), D35.4 (VSS), D36.4 (VSS), D37.4 (VSS), D38.4 (VSS), D39.4 (VSS), D40.4 (VSS), D41.4 (VSS), D42.4 (VSS), D44.4 (VSS), D45.4 (VSS), D46.4 (VSS), D47.4 (VSS), D48.4 (VSS), D49.4 (VSS), IC1.4 (GND), J1.A1 (GND), J1.A12 (GND), J1.B1 (GND), J1.B12 (GND), J1.S1 (SHIELD), R1.1, R2.1, SW2.1, U1.2 (GND), U2.3 (GND), U3.19 (TESTEN), U3.57 (GND), U4.3 (GND), U5.3 (GND), U6.3 (GND), U7.3 (GND), U8.3 (GND), U9.3 (GND), U10.3 (GND), U11.3 (GND), U12.3 (GND), U13.3 (GND), U14.3 (GND), U15.3 (GND), U16.3 (GND), U17.3 (GND), U18.3 (GND), U19.3 (GND), U20.3 (GND), U21.3 (GND), U22.3 (GND), U23.3 (GND), U24.3 (GND), U25.3 (GND), U26.3 (GND), U27.3 (GND), U28.3 (GND), U29.3 (GND), U30.3 (GND), U31.3 (GND), U32.3 (GND), U33.3 (GND), U34.3 (GND), U35.3 (GND), U36.3 (GND), U37.3 (GND), U38.3 (GND), U39.3 (GND), U40.3 (GND), U41.3 (GND), U42.3 (GND), U43.3 (GND), U44.3 (GND), U45.3 (GND), U46.1, U46.3 (GND), U47.3 (GND), U48.3 (GND), U49.3 (GND), U50.3 (GND), Y2.2, Y2.4
K_1: AM1.21 (I10), U4.2 (OUT)
K_2: AM1.23 (I8), U5.2 (OUT)
K_3: AM1.3 (I6), U2.2 (OUT)
K_4: AM1.4 (I5), U6.2 (OUT)
K_5: AM2.20 (I11), U7.2 (OUT)
K_6: AM2.21 (I10), U8.2 (OUT)
K_7: AM2.23 (I8), U9.2 (OUT)
K_8: AM2.2 (I7), U10.2 (OUT)
K_9: AM2.7 (I2), U13.2 (OUT)
K_10: AM3.21 (I10), U14.2 (OUT)
K_11: AM3.22 (I9), U11.2 (OUT)
K_12: AM3.4 (I5), U12.2 (OUT)
K_13: AM1.20 (I11), U15.2 (OUT)
K_14: AM1.22 (I9), U16.2 (OUT)
K_15: AM1.5 (I4), U23.2 (OUT)
K_16: AM1.2 (I7), U24.2 (OUT)
K_17: AM2.19 (I12), U17.2 (OUT)
K_18: AM2.22 (I9), U18.2 (OUT)
K_19: AM2.3 (I6), U19.2 (OUT)
K_20: AM2.4 (I5), U20.2 (OUT)
K_21: AM3.23 (I8), U25.2 (OUT)
K_22: AM3.20 (I11), U26.2 (OUT)
K_23: AM3.18 (I13), U21.2 (OUT)
K_24: AM3.3 (I6), U22.2 (OUT)
K_25: AM1.19 (I12), U27.2 (OUT)
K_26: AM1.17 (I14), U28.2 (OUT)
K_27: AM1.7 (I2), U35.2 (OUT)
K_28: AM1.8 (I1), U36.2 (OUT)
K_29: AM2.18 (I13), U29.2 (OUT)
K_30: AM2.16 (I15), U30.2 (OUT)
K_31: AM2.6 (I3), U31.2 (OUT)
K_32: AM2.8 (I1), U32.2 (OUT)
K_33: AM3.16 (I15), U37.2 (OUT)
K_34: AM3.17 (I14), U38.2 (OUT)
K_35: AM3.8 (I1), U33.2 (OUT)
K_36: AM3.6 (I3), U34.2 (OUT)
K_37: AM1.18 (I13), U39.2 (OUT)
K_38: AM1.16 (I15), U40.2 (OUT)
K_39: AM1.9 (I0), U47.2 (OUT)
K_40: AM1.6 (I3), U48.2 (OUT)
K_41: AM2.17 (I14), U41.2 (OUT)
K_42: AM2.5 (I4), U42.2 (OUT)
K_43: AM2.9 (I0), U43.2 (OUT)
K_44: AM3.19 (I12), U44.2 (OUT)
K_45: AM3.9 (I0), U49.2 (OUT)
K_46: AM3.7 (I2), U50.2 (OUT)
K_47: AM3.5 (I4), U45.2 (OUT)
unnamed: C24.1, R11.2, Y2.1
unnamed: D2.3 (DIN), D3.2 (DOUT)
unnamed: D3.3 (DIN), D4.2 (DOUT)
unnamed: D4.3 (DIN), D5.2 (DOUT)
unnamed: D5.3 (DIN), D6.2 (DOUT)
unnamed: D6.3 (DIN), D7.2 (DOUT)
unnamed: D7.3 (DIN), D8.2 (DOUT)
unnamed: D8.3 (DIN), D9.2 (DOUT)
unnamed: D10.3 (DIN), D11.2 (DOUT)
unnamed: D9.3 (DIN), D10.2 (DOUT)
unnamed: D11.3 (DIN), D12.2 (DOUT)
unnamed: D12.3 (DIN), D13.2 (DOUT)
unnamed: D14.3 (DIN), D15.2 (DOUT)
unnamed: D14.2 (DOUT), D25.3 (DIN)
unnamed: D15.3 (DIN), D16.2 (DOUT)
unnamed: D16.3 (DIN), D17.2 (DOUT)
unnamed: D17.3 (DIN), D18.2 (DOUT)
unnamed: D18.3 (DIN), D19.2 (DOUT)
unnamed: D2.2 (DOUT), D19.3 (DIN)
unnamed: D20.3 (DIN), D21.2 (DOUT)
unnamed: D20.2 (DOUT), D31.3 (DIN)
unnamed: D21.3 (DIN), D22.2 (DOUT)
unnamed: D22.3 (DIN), D23.2 (DOUT)
unnamed: D23.3 (DIN), D24.2 (DOUT)
unnamed: D24.3 (DIN), D25.2 (DOUT)
unnamed: D26.3 (DIN), D27.2 (DOUT)
unnamed: D26.2 (DOUT), D37.3 (DIN)
unnamed: D27.3 (DIN), D28.2 (DOUT)
unnamed: D28.3 (DIN), D29.2 (DOUT)
unnamed: D29.3 (DIN), D30.2 (DOUT)
unnamed: D30.3 (DIN), D31.2 (DOUT)
unnamed: D32.3 (DIN), D33.2 (DOUT)
unnamed: D32.2 (DOUT), D42.3 (DIN)
unnamed: D33.3 (DIN), D34.2 (DOUT)
unnamed: D34.3 (DIN), D35.2 (DOUT)
unnamed: D35.3 (DIN), D36.2 (DOUT)
unnamed: D36.3 (DIN), D37.2 (DOUT)
unnamed: D38.3 (DIN), D39.2 (DOUT)
unnamed: D38.2 (DOUT), D49.3 (DIN)
unnamed: D39.3 (DIN), D40.2 (DOUT)
unnamed: D40.3 (DIN), D41.2 (DOUT)
unnamed: D41.3 (DIN), D42.2 (DOUT)
unnamed: D44.3 (DIN), D45.2 (DOUT)
unnamed: D45.3 (DIN), D46.2 (DOUT)
unnamed: D46.3 (DIN), D47.2 (DOUT)
unnamed: D47.3 (DIN), D48.2 (DOUT)
unnamed: D48.3 (DIN), D49.2 (DOUT)
unnamed: J1.A5 (CC1), R1.2
unnamed: J1.B5 (CC2), R2.2
unnamed: R8.2, U3.46 (USB_DM)
unnamed: R7.2, U3.47 (USB_DP)
RGB: D13.3 (DIN), U46.4
RGB MCU: U3.8 (GPIO6), U46.2
SELECT0: AM1.10 (S0), AM2.10 (S0), AM3.10 (S0), U3.35 (GPIO23)
SELECT1: AM1.11 (S1), AM2.11 (S1), AM3.11 (S1), U3.29 (GPIO18)
SELECT2: AM1.14 (S2), AM2.14 (S2), AM3.14 (S2), U3.31 (GPIO20)
SELECT3: AM1.13 (S3), AM2.13 (S3), AM3.13 (S3), U3.28 (GPIO17)
USB_D+: D1.2 (I/O1), J1.A6 (D+), J1.B6 (D+), R7.1
USB_D-: D1.3 (I/O2), J1.A7 (D-), J1.B7 (D-), R8.1
VBUS: F1.1, J1.A4 (VBUS), J1.A9 (VBUS), J1.B4 (VBUS), J1.B9 (VBUS)

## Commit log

2023-08-20 initialise
2023-08-20 deleted caps, res from moon project
2023-08-24 vootvan progress
2023-08-29 continue progress
2023-09-15 project folder update
2023-09-15 backup
2023-09-24 created production files
2023-09-25 production files, back silkscreen
2023-10-01 created v4n pcb, finished routing
2023-10-11 updated VAN and V4N projects
2023-10-29 created plates and production files for protos
2023-12-02 rgb footprints changed, fresh gerbers, production
2024-05-07 pin revision
2024-08-28 revision work
2025-01-05 g0b1 revision added
2025-01-05 backups
2025-02-11 revision proto ready
    folder clean up
2025-03-23 production files pcb&plate
    before second order
2025-05-03 project clean up
2025-05-09 power error fix
2025-08-14 reference
2026-02-21 update repo for release
